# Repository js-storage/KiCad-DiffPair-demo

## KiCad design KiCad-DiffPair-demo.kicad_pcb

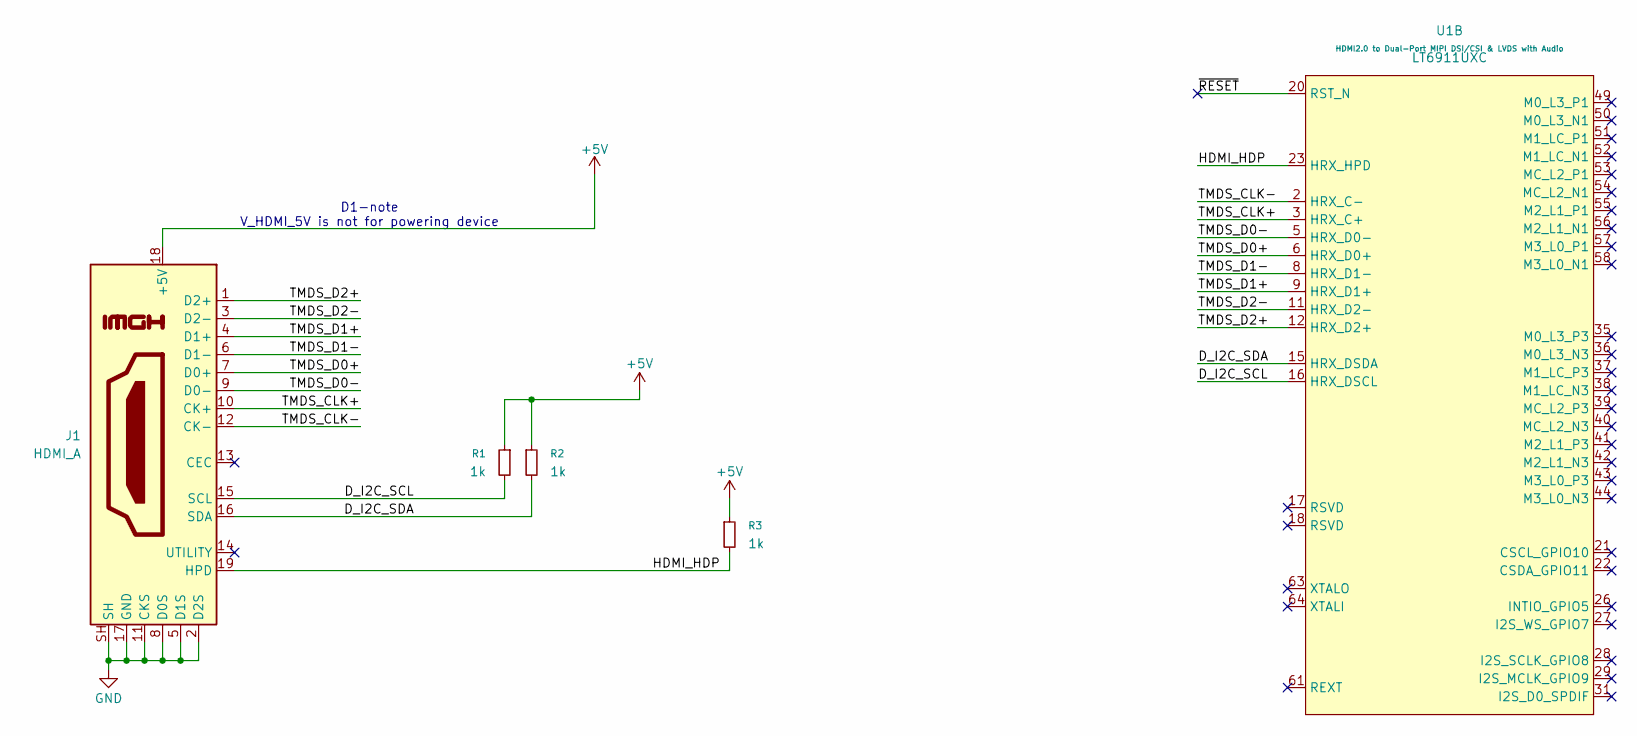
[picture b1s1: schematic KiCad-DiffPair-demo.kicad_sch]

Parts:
J1: HDMI_A; HDMI_A_Amphenol_10029449-x01xLF_Horizontal
R1, R2, R3: 1k; R_0603_1608Metric
U1: IO_HDMI_LT6911UXC_QFN-64; QFN-64-1EP_8x8mm_P0.4mm_EP6.5x6.5mm; part_value LT6911UXC

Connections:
+5V: J1.18 (+5V), R1.1, R2.1, R3.1
/D_I2C_SCL: J1.15 (SCL), R1.2, U1.16 (HRX_DSCL)
/D_I2C_SDA: J1.16 (SDA), R2.2, U1.15 (HRX_DSDA)
/HDMI_HDP: J1.19 (HPD), R3.2, U1.23 (HRX_HPD)
/TMDS_CLK+: J1.10 (CK+), U1.3 (HRX_C+)
/TMDS_CLK-: J1.12 (CK-), U1.2 (HRX_C-)
/TMDS_D0+: J1.7 (D0+), U1.6 (HRX_D0+)
/TMDS_D0-: J1.9 (D0-), U1.5 (HRX_D0-)
/TMDS_D1+: J1.4 (D1+), U1.9 (HRX_D1+)
/TMDS_D1-: J1.6 (D1-), U1.8 (HRX_D1-)
/TMDS_D2+: J1.1 (D2+), U1.12 (HRX_D2+)
/TMDS_D2-: J1.3 (D2-), U1.11 (HRX_D2-)
/~RESET: U1.20 (RST_N)
GND: J1.2 (D2S), J1.5 (D1S), J1.8 (D0S), J1.11 (CKS), J1.17 (GND), J1.SH

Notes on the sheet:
D1-note V_HDMI_5V is not for powering device

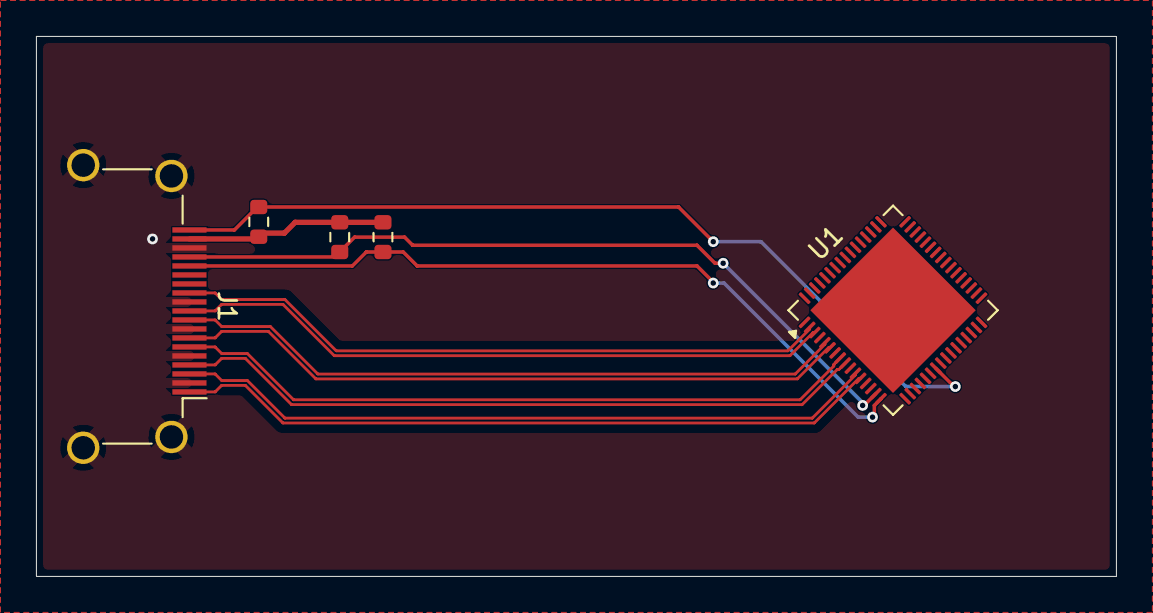
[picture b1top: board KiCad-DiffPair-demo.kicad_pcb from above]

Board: 4 copper layers, 60.0 x 30.0 mm, 5 parts (0 on the bottom side), 13 nets.

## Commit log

2026-05-25 Init
2026-05-26 Uprava diff pair, Uprava pravidla
2026-05-26 Verze 01
